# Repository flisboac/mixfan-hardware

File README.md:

# mixfan-hardware

Hardware for the Mixfan, an USB-connected and powered 12V fan controller, that uses as much stock/cheap parts as possible. 

> TODO: PCB layout

Schematics: [docs/production/usb-fan-controller.pdf](docs/production/usb-fan-controller.pdf)

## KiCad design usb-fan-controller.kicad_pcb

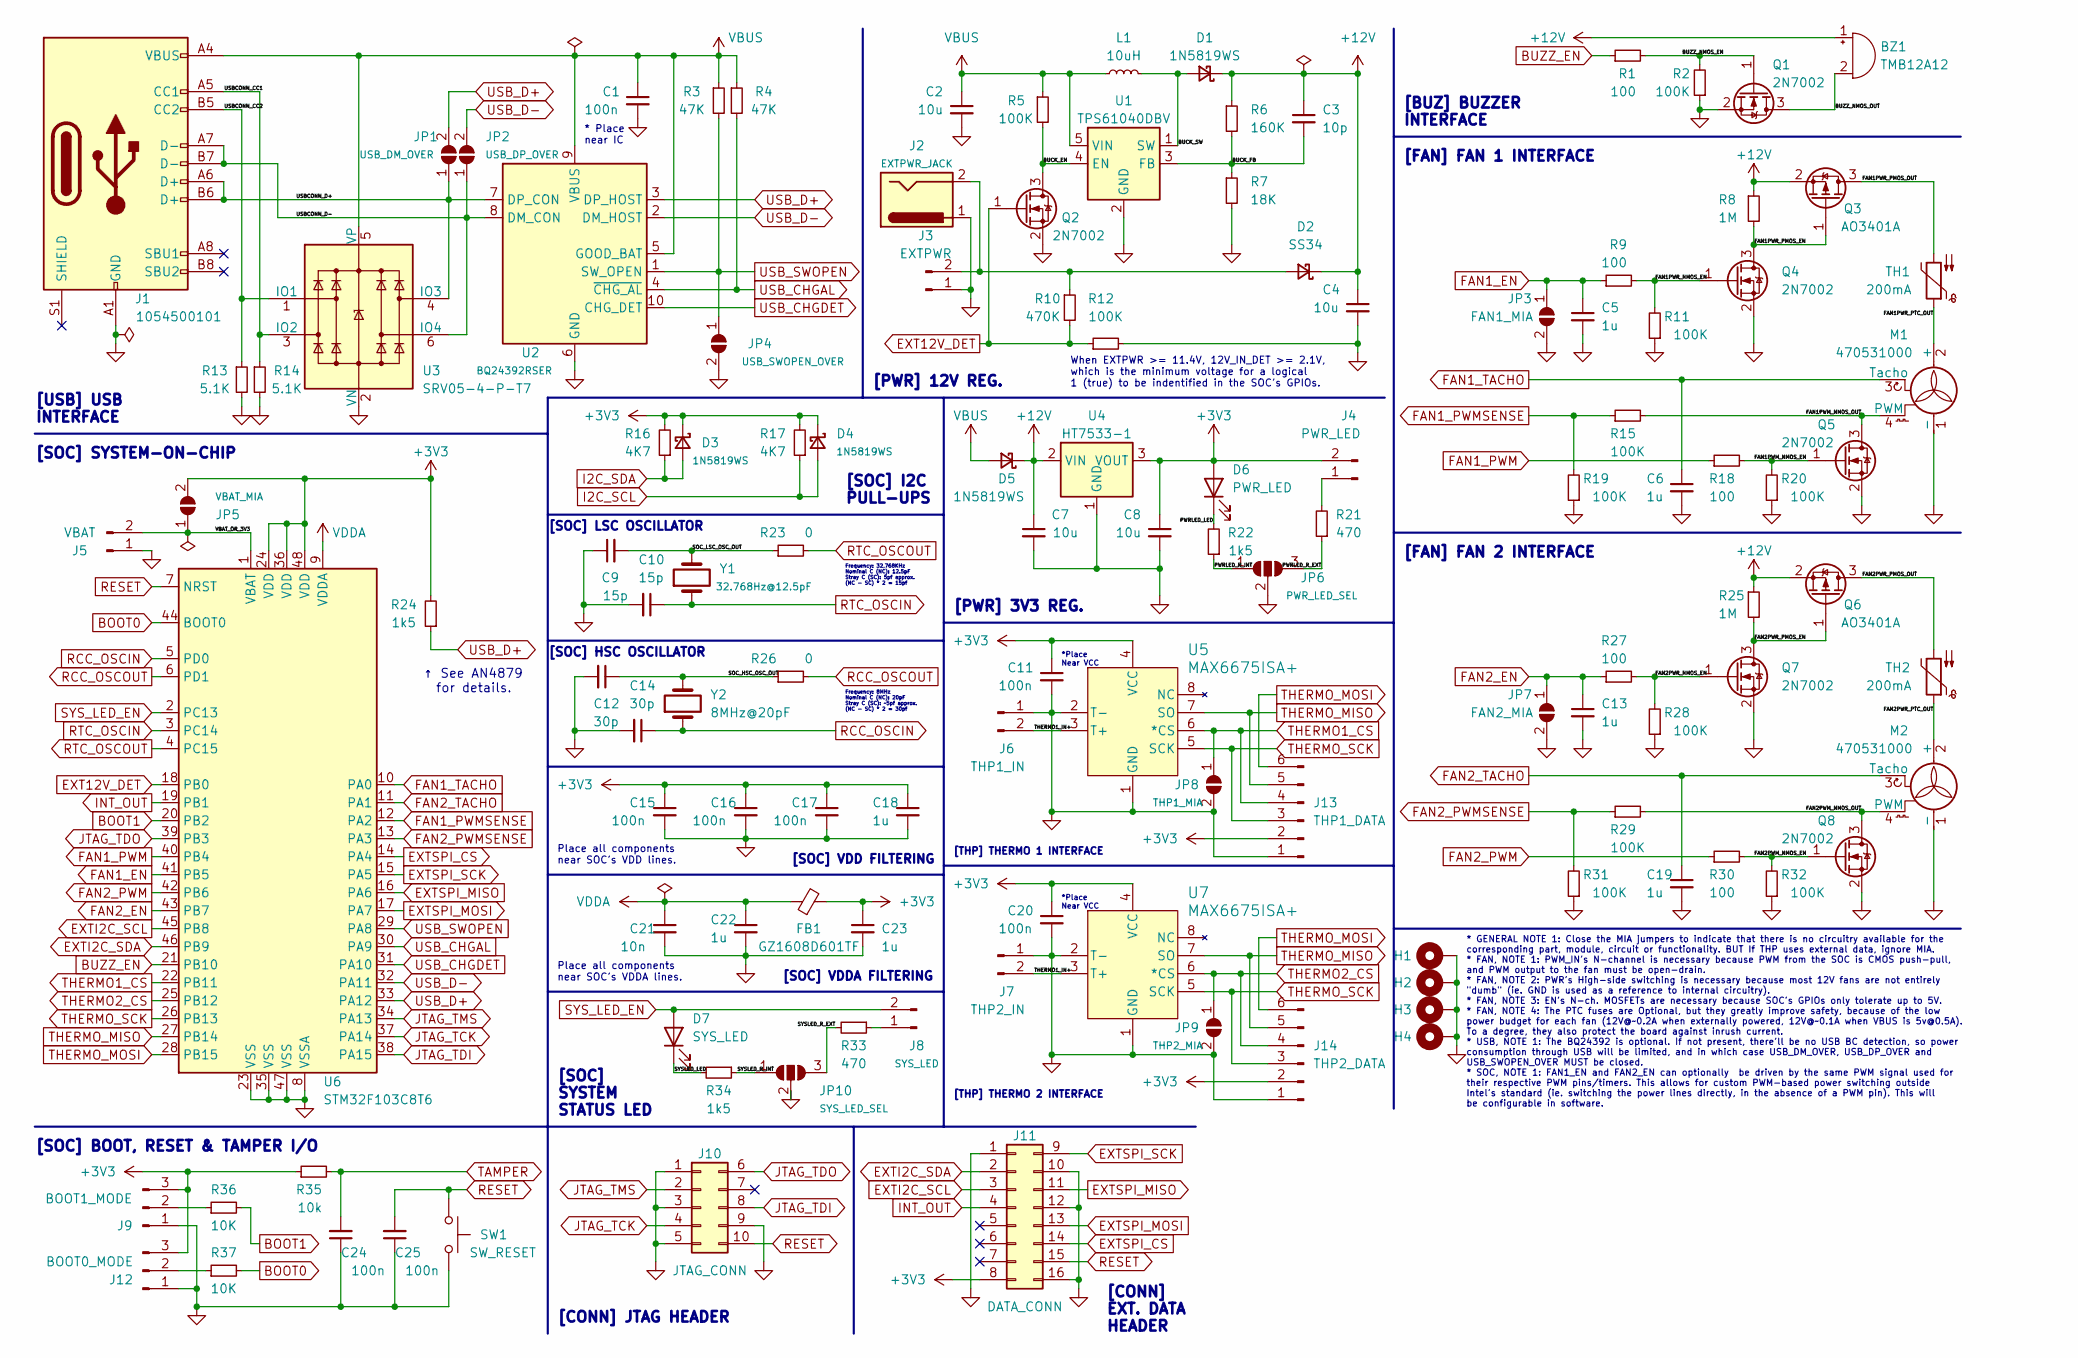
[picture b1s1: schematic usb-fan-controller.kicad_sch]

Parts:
BZ1: TMB12A12; Buzzer_12x9.5RM7.6; JLCPCB Part C96079
C1, C11, C15, C16, C17, C20, C24, C25: 100n; C_0402_1005Metric_Pad0.74x0.62mm_HandSolder
C2, C4, C7, C8: 10u; C_0603_1608Metric; JLCPCB Part C96446
C3: 10p; C_0402_1005Metric; JLCPCB Part C32949
C5, C6, C13, C18, C19, C22, C23: 1u; C_0402_1005Metric; JLCPCB Part C52923
C9, C10: 15p; C_0402_1005Metric_Pad0.74x0.62mm_HandSolder; JLCPCB Part C32949
C12, C14: 30p; C_0603_1608Metric; JLCPCB Part C1658
C21: 10n; C_0402_1005Metric_Pad0.74x0.62mm_HandSolder; JLCPCB Part C15195
D1, D3, D4, D5: 1N5819WS; D_SOD-323
D2: SS34; D_SMA; JLCPCB Part C8678
D6: PWR_LED; D_0603_1608Metric; JLCPCB Part C2286
D7: SYS_LED; D_0603_1608Metric; JLCPCB Part C2286
FB1: GZ1608D601TF; L_0603_1608Metric
H1, H2, H3, H4: MountingHole_Pad; MountingHole_2.2mm_M2_Pad_Via
J1: 1054500101; USB_C_Receptacle_Molex_105450-0101; JLCPCB Part C134092
J2: EXTPWR_JACK; BarrelJack_CLIFF_FC681465S_SMT_Horizontal
J3: EXTPWR; TerminalBlock_bornier-2_P5.08mm; JLCPCB Part C8465
J4: PWR_LED; LED_D3.0mm; JLCPCB Part C8465
J5: VBAT; JST_PH_B2B-PH-K_1x02_P2.00mm_Vertical; JLCPCB Part C8465
J6: THP1_IN; TerminalBlock_bornier-2_P5.08mm; JLCPCB Part C8465
J7: THP2_IN; TerminalBlock_bornier-2_P5.08mm; JLCPCB Part C8465
J8: SYS_LED; LED_D3.0mm; JLCPCB Part C8465
J9: BOOT1_MODE; PinHeader_1x03_P2.54mm_Vertical
J10: JTAG_CONN; PinHeader_2x05_P2.54mm_Horizontal
J11: DATA_CONN; PinHeader_2x08_P2.54mm_Vertical
J12: BOOT0_MODE; PinHeader_1x03_P2.54mm_Vertical
J13: THP1_DATA
J14: THP2_DATA; PinHeader_1x06_P2.54mm_Horizontal
JP1: USB_DM_OVER; SolderJumper-2_P1.3mm_Open_RoundedPad1.0x1.5mm
JP2: USB_DP_OVER; SolderJumper-2_P1.3mm_Open_RoundedPad1.0x1.5mm
JP3: FAN1_MIA; SolderJumper-2_P1.3mm_Open_RoundedPad1.0x1.5mm
JP4: USB_SWOPEN_OVER; SolderJumper-2_P1.3mm_Open_RoundedPad1.0x1.5mm
JP5: VBAT_MIA; SolderJumper-2_P1.3mm_Open_RoundedPad1.0x1.5mm
JP6: PWR_LED_SEL; SolderJumper-3_P1.3mm_Open_RoundedPad1.0x1.5mm
JP7: FAN2_MIA; SolderJumper-2_P1.3mm_Open_RoundedPad1.0x1.5mm
JP8: THP1_MIA; SolderJumper-2_P1.3mm_Open_RoundedPad1.0x1.5mm
JP9: THP2_MIA; SolderJumper-2_P1.3mm_Open_RoundedPad1.0x1.5mm
JP10: SYS_LED_SEL; SolderJumper-3_P1.3mm_Open_RoundedPad1.0x1.5mm
L1: 10uH; L_0805_2012Metric_Pad1.15x1.40mm_HandSolder; LCSC Part C426327
M1, M2: 470531000; FanPinHeader_1x04_P2.54mm_Vertical
Q1, Q2, Q4, Q5, Q7, Q8: 2N7002; SOT-23
Q3, Q6: AO3401A; SOT-23
R1, R9, R18, R27, R30: 100; R_0402_1005Metric_Pad0.72x0.64mm_HandSolder
R2, R5, R11, R12, R15, R19, R20, R28, R29, R31, R32: 100K; R_0402_1005Metric_Pad0.72x0.64mm_HandSolder
R3, R4: 47K; R_0402_1005Metric_Pad0.72x0.64mm_HandSolder
R6: 160K; R_0603_1608Metric; JLCPCB Part C1035
R7: 18K; R_0603_1608Metric; JLCPCB Part C25810
R8, R25: 1M; R_0402_1005Metric_Pad0.72x0.64mm_HandSolder
R10: 470K; R_0603_1608Metric; JLCPCB Part C23178
R13, R14: 5.1K; R_0402_1005Metric_Pad0.72x0.64mm_HandSolder
R16, R17: 4K7; R_0402_1005Metric_Pad0.72x0.64mm_HandSolder
R21, R33: 470; R_0402_1005Metric_Pad0.72x0.64mm_HandSolder
R22, R24, R34: 1k5; R_0402_1005Metric_Pad0.72x0.64mm_HandSolder
R23, R26: 0; R_0402_1005Metric_Pad0.72x0.64mm_HandSolder
R35: 10k; R_0402_1005Metric_Pad0.72x0.64mm_HandSolder
R36, R37: 10K; R_0402_1005Metric_Pad0.72x0.64mm_HandSolder
SW1: SW_RESET; SW_SPST_SKQG_WithStem; JLCPCB Part C318884
TH1, TH2: 200mA; R_0603_1608Metric; JLCPCB Part C883092
U1: TPS61040DBV; SOT-23-5; JLCPCB Part C7722
U2: BQ24392RSER; Texas_R-PUQFN-N10
U3: SRV05-4-P-T7; SOT-23-6; JLCPCB Part C85364
U4: HT7533-1; SOT-89-3; JLCPCB Part C14289
U5, U7: MAX6675ISA+; MAX6675ISA
U6: STM32F103C8T6; LQFP-48_7x7mm_P0.5mm; JLCPCB Part C8734
Y1: 32.768Hz@12.5pF; Crystal_SMD_3215-2Pin_3.2x1.5mm; JLCPCB Part C32346
Y2: 8MHz@20pF; Crystal_SMD_5032-2Pin_5.0x3.2mm; JLCPCB Part C115962

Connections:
+3V3: C8.1, C11.1, C15.1, C16.1, C17.1, C18.1, C20.1, C23.1, D3.1 (K), D4.1 (K), D6.2 (A), FB1.2, J4.2, J9.3, J11.8, J12.3, J13.2, J14.2, JP5.2 (B), R16.2, R17.2, R24.2, R35.1, U4.3 (VOUT), U5.4 (VCC), U6.24 (VDD), U6.36 (VDD), U6.48 (VDD), U7.4 (VCC)
+12V: BZ1.1 (-), C3.1, C4.1, C7.1, D1.1 (K), D2.1 (K), D5.1 (K), Q3.2 (S), Q6.2 (S), R6.1, R8.1, R25.1, U4.2 (VIN)
/BUCK_EN: Q2.3 (D), R5.2, U1.4 (EN)
/BUCK_FB: C3.2, R6.2, R7.1, U1.3 (FB)
/BUCK_SW: D1.2 (A), L1.2, U1.1 (SW)
/BUZZ_NMOS_EN: Q1.1 (G), R1.2, R2.2
/BUZZ_NMOS_OUT: BZ1.2 (+), Q1.3 (D)
/FAN1PWM_NMOS_EN: Q5.1 (G), R18.2, R20.2
/FAN1PWM_NMOS_OUT: M1.4 (PWM), Q5.3 (D), R15.2
/FAN1PWR_NMOS_EN: Q4.1 (G), R9.2, R11.2
/FAN1PWR_PMOS_EN: Q3.1 (G), Q4.3 (D), R8.2
/FAN1PWR_PMOS_OUT: Q3.3 (D), TH1.2
/FAN1PWR_PTC_OUT: M1.2 (+), TH1.1
/FAN2PWM_NMOS_EN: Q8.1 (G), R30.2, R32.2
/FAN2PWM_NMOS_OUT: M2.4 (PWM), Q8.3 (D), R29.2
/FAN2PWR_NMOS_EN: Q7.1 (G), R27.2, R28.2
/FAN2PWR_PMOS_EN: Q6.1 (G), Q7.3 (D), R25.2
/FAN2PWR_PMOS_OUT: Q6.3 (D), TH2.2
/FAN2PWR_PTC_OUT: M2.2 (+), TH2.1
/PWRLED_LED: D6.1 (K), R22.2
/PWRLED_R_EXT: JP6.3 (B), R21.1
/PWRLED_R_INT: JP6.1 (A), R22.1
/SOC_HSC_OSC_OUT: C12.1, R26.1, Y2.2
/SOC_LSC_OSC_OUT: C9.2, R23.1, Y1.2
/SYSLED_LED: D7.1 (K), R34.2
/SYSLED_R_EXT: JP10.3 (B), R33.2
/SYSLED_R_INT: JP10.1 (A), R34.1
/THERMO1_IN+: J6.2, J7.2, U5.3 (T+), U7.3 (T+)
/USBCONN_CC1: J1.A5 (CC1), R14.1, U3.3 (IO2)
/USBCONN_CC2: J1.B5 (CC2), R13.1, U3.1 (IO1)
/USBCONN_D+: J1.A6 (D+), J1.B6 (D+), JP1.1 (A), U2.7 (DP_CON), U3.4 (IO3)
/USBCONN_D-: J1.A7 (D-), J1.B7 (D-), JP2.1 (A), U2.8 (DM_CON), U3.6 (IO4)
/VBAT_OR_3V3: J5.2, JP5.1 (A), U6.1 (VBAT)
BOOT0: R37.2, U6.44 (BOOT0)
BOOT1: R36.2, U6.20 (PB2)
BUZZ_EN: R1.1, U6.21 (PB10)
EXT12V_DET: Q2.1 (G), R10.2, R12.1, U6.18 (PB0)
EXTI2C_SCL: J11.3, U6.45 (PB8)
EXTI2C_SDA: J11.2, U6.46 (PB9)
EXTSPI_CS: J11.14, U6.14 (PA4)
EXTSPI_MISO: J11.11, U6.16 (PA6)
EXTSPI_MOSI: J11.13, U6.17 (PA7)
EXTSPI_SCK: J11.9, U6.15 (PA5)
FAN1_EN: C5.1, JP3.1 (A), R9.1, U6.41 (PB5)
FAN1_PWM: R18.1, U6.40 (PB4)
FAN1_PWMSENSE: R15.1, R19.2, U6.12 (PA2)
FAN1_TACHO: C6.1, M1.3 (Tacho), U6.10 (PA0)
FAN2_EN: C13.1, JP7.1 (A), R27.1, U6.43 (PB7)
FAN2_PWM: R30.1, U6.42 (PB6)
FAN2_PWMSENSE: R29.1, R31.2, U6.13 (PA3)
FAN2_TACHO: C19.1, M2.3 (Tacho), U6.11 (PA1)
GND: C1.2, C2.2, C4.2, C5.2, C6.2, C7.2, C8.2, C9.1, C10.2, C11.2, C12.2, C13.2, C14.2, C15.2, C16.2, C17.2, C18.2, C19.2, C20.2, C21.2, C22.2, C23.2, C24.1, C25.1, H1.1, H2.1, H3.1, H4.1, J1.A1 (GND), J1.A12 (GND), J1.B1 (GND), J1.B12 (GND), J2.1, J3.1, J5.1, J6.1, J7.1, J9.1, J10.1, J10.3, J10.5, J10.9, J11.1, J11.10, J11.12, J11.16, J12.1, J13.1, J14.1, JP3.2 (B), JP4.2 (B), JP6.2 (C), JP7.2 (B), JP8.2 (B), JP9.2 (B), JP10.2 (C), M1.1 (-), M2.1 (-), Q1.2 (S), Q2.2 (S), Q4.2 (S), Q5.2 (S), Q7.2 (S), Q8.2 (S), R2.1, R7.2, R11.1, R12.2, R13.2, R14.2, R19.1, R20.1, R28.1, R31.1, R32.1, SW1.1, U1.2 (GND), U2.6 (GND), U3.2 (VN), U4.1 (GND), U5.1 (GND), U5.2 (T-), U6.8 (VSSA), U6.23 (VSS), U6.35 (VSS), U6.47 (VSS), U7.1 (GND), U7.2 (T-)
I2C_SCL: D4.2 (A), R17.1
I2C_SDA: D3.2 (A), R16.1
INT_OUT: J11.4, U6.19 (PB1)
JTAG_TCK: J10.4, U6.37 (PA14)
JTAG_TDI: J10.8, U6.38 (PA15)
JTAG_TDO: J10.6, U6.39 (PB3)
JTAG_TMS: J10.2, U6.34 (PA13)
unnamed: D2.2 (A), J2.2, J3.2, R10.1
unnamed: J4.1, R21.2
unnamed: J8.1, R33.1
unnamed: J9.2, R36.1
unnamed: J12.2, R37.1
RCC_OSCIN: C14.1, U6.5 (PD0), Y2.1
RCC_OSCOUT: R26.2, U6.6 (PD1)
RESET: C25.2, J10.10, J11.15, SW1.2, U6.7 (NRST)
RTC_OSCIN: C10.1, U6.3 (PC14), Y1.1
RTC_OSCOUT: R23.2, U6.4 (PC15)
SYS_LED_EN: D7.2 (A), J8.2, U6.2 (PC13)
TAMPER: C24.2, R35.2
THERMO1_CS: J13.4, JP8.1 (A), U5.6 (*CS), U6.22 (PB11)
THERMO2_CS: J14.4, JP9.1 (A), U6.25 (PB12), U7.6 (*CS)
THERMO_MISO: J13.5, J14.5, U5.7 (SO), U6.27 (PB14), U7.7 (SO)
THERMO_MOSI: J13.6, J14.6, U6.28 (PB15)
THERMO_SCK: J13.3, J14.3, U5.5 (SCK), U6.26 (PB13), U7.5 (SCK)
USB_CHGAL: R4.2, U2.4 (~CHG_AL), U6.30 (PA9)
USB_CHGDET: U2.10 (CHG_DET), U6.31 (PA10)
USB_D+: JP1.2 (B), R24.1, U2.3 (DP_HOST), U6.33 (PA12)
USB_D-: JP2.2 (B), U2.2 (DM_HOST), U6.32 (PA11)
USB_SWOPEN: JP4.1 (A), R3.2, U2.1 (SW_OPEN), U6.29 (PA8)
VBUS: C1.1, C2.1, D5.2 (A), J1.A4 (VBUS), J1.A9 (VBUS), J1.B4 (VBUS), J1.B9 (VBUS), L1.1, R3.1, R4.1, R5.1, U1.5 (VIN), U2.5 (GOOD_BAT), U2.9 (VBUS), U3.5 (VP)
VDDA: C21.1, C22.1, FB1.1, U6.9 (VDDA)

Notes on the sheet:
* Place near IC
*Place Near VCC
When EXTPWR >= 11.4V, 12V_IN_DET >= 2.1V, which is the minimum voltage for a logical 1 (true) to be indentified in the SOC's GPIOs.
[USB] USB INTERFACE
[CONN] EXT. DATA HEADER
↑ See AN4879 for details.
Frequency: 32,768KHz Nominal C (NC): 12.5pF Stray C (SC): 5pf approx. (NC - SC) * 2 = 15pf
[PWR] 12V REG.
* GENERAL NOTE 1: Close the MIA jumpers to indicate that there is no circuitry available for the corresponding part, module, circuit or functionality. BUT If THP uses external data, ignore MIA. * FAN, NOTE 1: PWM_IN's N-channel is necessary because PWM from the SOC is CMOS push-pull, and PWM output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
[FAN] FAN 2 INTERFACE
Place all components near SOC's VDD lines.
[FAN] FAN 1 INTERFACE
[SOC] LSC OSCILLATOR
[SOC] SYSTEM STATUS LED
Place all components near SOC's VDDA lines.
[SOC] SYSTEM-ON-CHIP
[THP] THERMO 1 INTERFACE
[SOC] BOOT, RESET & TAMPER I/O
[CONN] JTAG HEADER
[SOC] I2C PULL-UPS
Frequency: 8MHz Nominal C (NC): 20pF Stray C (SC): ~5pf approx. (NC - SC) * 2 = 30pf
[BUZ] BUZZER INTERFACE
[SOC] VDDA FILTERING
[THP] THERMO 2 INTERFACE
[PWR] 3V3 REG.
[SOC] VDD FILTERING
[SOC] HSC OSCILLATOR

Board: 2 copper layers, 122 parts (0 on the bottom side), 83 nets, no tracks yet.

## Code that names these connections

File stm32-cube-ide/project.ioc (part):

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Mcu.Name=STM32F103C(8-B)Tx
Mcu.Package=LQFP48
Mcu.UserName=STM32F103C8Tx
PA0-WKUP.GPIOParameters=GPIO_Label
PA0-WKUP.GPIO_Label=FAN1_TACHO
PA0-WKUP.Signal=ADCx_IN0
PA1.GPIOParameters=GPIO_Label
PA1.GPIO_Label=FAN2_TACHO
PA1.Signal=ADCx_IN1
PA10.GPIOParameters=GPIO_Label
PA10.GPIO_Label=USB_CHGDET
PA10.Signal=GPIO_Input
PA11.Mode=Device
PA11.Signal=USB_DM
PA12.Mode=Device
PA12.Signal=USB_DP
PA13.GPIOParameters=GPIO_Label
PA13.GPIO_Label=JTAG_TMS
PA13.Mode=JTAG_4_pins
PA13.Signal=SYS_JTMS-SWDIO
PA14.GPIOParameters=GPIO_Label
PA14.GPIO_Label=JTAG_TCK
PA14.Mode=JTAG_4_pins
PA14.Signal=SYS_JTCK-SWCLK
PA15.GPIOParameters=GPIO_Label
PA15.GPIO_Label=JTAG_TDI
PA15.Mode=JTAG_4_pins
PA15.Signal=SYS_JTDI
PA2.GPIOParameters=GPIO_Label
PA2.GPIO_Label=FAN1_PWMSENSE
PA2.Signal=ADCx_IN2
PA3.GPIOParameters=GPIO_Label
PA3.GPIO_Label=FAN2_PWMSENSE
PA3.Signal=ADCx_IN3
PA4.GPIOParameters=GPIO_Label
PA4.GPIO_Label=EXTSPI_CS
PA4.Mode=NSS_Signal_Hard_Input
PA4.Signal=SPI1_NSS
PA5.GPIOParameters=GPIO_Label
PA5.GPIO_Label=EXTSPI_SCK
PA5.Mode=Full_Duplex_Slave
PA5.Signal=SPI1_SCK
PA6.GPIOParameters=GPIO_Label
PA6.GPIO_Label=EXTSPI_MISO
PA6.Mode=Full_Duplex_Slave
PA6.Signal=SPI1_MISO
PA7.GPIOParameters=GPIO_Label
PA7.GPIO_Label=EXTSPI_MOSI
PA7.Mode=Full_Duplex_Slave
PA7.Signal=SPI1_MOSI
PA8.GPIOParameters=GPIO_Label
PA8.GPIO_Label=USB_SWOPEN
PA8.Signal=GPIO_Input
PA9.GPIOParameters=GPIO_Label
PA9.GPIO_Label=USB_CHGAL
PA9.Signal=GPIO_Input
PB0.GPIOParameters=GPIO_Label
PB0.GPIO_Label=EXT12V_DET
PB0.Signal=ADCx_IN8
PB1.GPIOParameters=GPIO_Label
PB1.GPIO_Label=INT_OUT
PB1.Signal=GPIO_Output
PB10.GPIOParameters=GPIO_Label
PB10.GPIO_Label=BUZZ_EN
PB10.Signal=GPIO_Output
PB11.GPIOParameters=GPIO_Label
PB11.GPIO_Label=THERMO1_CS
PB11.Signal=GPIO_Output
PB12.GPIOParameters=GPIO_Label
PB12.GPIO_Label=THERMO2_CS
PB12.Signal=GPIO_Output
PB13.GPIOParameters=GPIO_Label
PB13.GPIO_Label=THERMO_SCK
PB13.Mode=Full_Duplex_Master
PB13.Signal=SPI2_SCK
PB14.GPIOParameters=GPIO_Label
PB14.GPIO_Label=THERMO_MISO
PB14.Mode=Full_Duplex_Master
PB14.Signal=SPI2_MISO
PB15.GPIOParameters=GPIO_Label
PB15.GPIO_Label=THERMO_MOSI
PB15.Mode=Full_Duplex_Master
PB15.Signal=SPI2_MOSI
PB3.GPIOParameters=GPIO_Label
PB3.GPIO_Label=JTAG_TDO
PB3.Mode=JTAG_4_pins
PB3.Signal=SYS_JTDO-TRACESWO
PB4.GPIOParameters=GPIO_Label
PB4.GPIO_Label=FAN1_PWM
PB4.Signal=S_TIM3_CH1
PB5.GPIOParameters=GPIO_Label
PB5.GPIO_Label=FAN1_EN
PB5.Signal=S_TIM3_CH2
PB6.GPIOParameters=GPIO_Label
PB6.GPIO_Label=FAN2_PWM
PB6.Signal=S_TIM4_CH1
PB7.GPIOParameters=GPIO_Label
PB7.GPIO_Label=FAN2_EN
PB7.Signal=S_TIM4_CH2
PB8.GPIOParameters=GPIO_Label
PB8.GPIO_Label=EXTI2C_SCL
PB8.Mode=I2C
PB8.Signal=I2C1_SCL
PB9.GPIOParameters=GPIO_Label
PB9.GPIO_Label=EXTI2C_SDA
PB9.Mode=I2C
PB9.Signal=I2C1_SDA
PC13-TAMPER-RTC.GPIOParameters=GPIO_Label
PC13-TAMPER-RTC.GPIO_Label=SYS_LED_EN
PC13-TAMPER-RTC.Signal=GPIO_Output
PC14-OSC32_IN.Mode=LSE-External-Oscillator
PC14-OSC32_IN.Signal=RCC_OSC32_IN
PC15-OSC32_OUT.Mode=LSE-External-Oscillator
PC15-OSC32_OUT.Signal=RCC_OSC32_OUT
PD0-OSC_IN.Mode=HSE-External-Oscillator
PD0-OSC_IN.Signal=RCC_OSC_IN
PD1-OSC_OUT.Mode=HSE-External-Oscillator
PD1-OSC_OUT.Signal=RCC_OSC_OUT
RCC.SYSCLKFreq_VALUE=72000000
RCC.SYSCLKSource=RCC_SYSCLKSOURCE_PLLCLK
board=custom

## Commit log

2023-09-25 feat: initial commit
2023-09-25 feat: add stm32-cube-ide project
2023-09-25 feat: add external THM SPI connection
2023-09-25 chore: update production docs
